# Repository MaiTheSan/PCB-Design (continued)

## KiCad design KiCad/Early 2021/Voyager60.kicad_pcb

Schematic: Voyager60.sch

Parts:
C1, C3, C4, C5, C9, C10, C11, C12, C13, C14, C15, C16, C17, C18, C19, C20, C21: 0.1uF; C_0603
C2: 10uF; C_0603
C6: 1uF; C_0603
C7, C8: 22pF; C_0603
D1, D2, D3, D4, D5, D6, D7, D8, D9, D10, D11, D12, D13, D14, D15, D16, D17, D18, D19, D20, D21, D22, D23, D24, D25, D26, D27, D28, D29, D30, D31, D32, D33, D34, D35, D36, D37, D38, D39, D40, D41, D42, D43, D45, D46, D47, D48, D49, D50, D51, D52, D53, D54, D55, D56, D57, D58, D59, D60, D61, D62, D63, D64, D65, D66, D67, D69: SOD-123; D_SOD-123
F1: 500mA; Fuse_SMD1206_Reflow
K_#1, K_#2, K_#3, K_#4, K_#5, K_#6, K_#7, K_#8, K_#9, K_#10: MX-1U; MXOnly-1U
K_'1: MX-1U; MXOnly-1U
K_,1: MX-1U; MXOnly-1U
K_-1: MX-1U; MXOnly-1U
K_.1: MX-1U; MXOnly-1U
K_/1: MX-1U; MXOnly-1U
K_;1: MX-1U; MXOnly-1U
K_=1: MX-1U; MXOnly-1U
K_A1: MX-1U; MXOnly-1U
K_ALT1: MX-1.25U; MXOnly-1.25U
K_ALT2: MX-1.5U; MXOnly-1.5U-FLIPPED
K_B1: MX-1U; MXOnly-1U
K_BACK1: MX-2U; MXOnly-2U
K_C1: MX-1U; MXOnly-1U
K_CAPS1: MX-1.75U; MXOnly-1.75U
K_CAPS2: MX-1.25U; MXOnly-1.25U-FLIPPED
K_CTRL1: MX-1.25U; MXOnly-1.25U
K_CTRL2: MX-1.5U; MXOnly-1.5U-FLIPPED
K_D1: MX-1U; MXOnly-1U
K_E1: MX-1U; MXOnly-1U
K_ENTER1: MX-2.25U; MXOnly-2.25U
K_ENTER2: MX-ISO; MXOnly-ISO-ROTATED-ReversedStabilizers
K_ESC1: MX-1U; MXOnly-1U
K_F1: MX-1U; MXOnly-1U
K_FNC1, K_FNC2, K_FNC3, K_FNC4, K_FNC5: MX-1U; MXOnly-1U-FLIPPED
K_G1: MX-1U; MXOnly-1U
K_H1: MX-1U; MXOnly-1U
K_I1: MX-1U; MXOnly-1U
K_J1: MX-1U; MXOnly-1U
K_K1: MX-1U; MXOnly-1U
K_L1: MX-1U; MXOnly-1U
K_M1: MX-1U; MXOnly-1U
K_N1: MX-1U; MXOnly-1U
K_O1: MX-1U; MXOnly-1U
K_P1: MX-1U; MXOnly-1U
K_Q1: MX-1U; MXOnly-1U
K_R1: MX-1U; MXOnly-1U
K_RALT2: MX-1.25U; MXOnly-1.25U-FLIPPED
K_RALT3: MX-1.5U; MXOnly-1.5U-FLIPPED
K_RCTRL2: MX-1U; MXOnly-1U
K_RMENU2: MX-1U; MXOnly-1U
K_RWIN2: MX-1.25U; MXOnly-1.25U
K_S1: MX-1U; MXOnly-1U
K_SHIFT1: MX-2.25U; MXOnly-2.25U
K_SPACE1: MX-7U; MXOnly-7U-ReversedStabilizers
K_SPACE2: MX-6.25U; MXOnly-6.25U-ReversedStabilizers
K_SRSHIFT1: MX-1.75U; MXOnly-1.75U
K_SRSHIFT2: MX-1U; MXOnly-1U
K_T1: MX-1U; MXOnly-1U
K_TAB1: MX-1.5U; MXOnly-1.5U
K_U1: MX-1U; MXOnly-1U
K_V1: MX-1U; MXOnly-1U
K_W1: MX-1U; MXOnly-1U
K_WIN1: MX-1.25U; MXOnly-1.25U
K_WIN2: MX-1U; MXOnly-1U-FLIPPED
K_X1: MX-1U; MXOnly-1U
K_Y1: MX-1U; MXOnly-1U
K_Z1: MX-1U; MXOnly-1U
K_[1: MX-1U; MXOnly-1U
K_\1: MX-1.5U; MXOnly-1.5U
K_\2: MX-1U; MXOnly-1U
K_]1: MX-1U; MXOnly-1U
Q1: 2N7002; SOT-23
R1, R2, R3, R4, R5, R6, R7, R8, R9, R10, R11, R12, R13, R14, R15, R16, R17, R18, R19, R20, R21, R22, R23, R24, R25, R26, R27, R28, R29, R30, R32, R33, R34, R35, R36, R37, R38, R39, R40, R41, R42, R43, R45, R46, R47, R48, R49, R50, R51, R52, R53, R54, R55, R56, R57, R58, R59, R60, R61, R62, R63, R64, R65, R66, R69, R71, R72, R76: 1k; R_0805
R31: 300; R_0805
R67, R68: 22; R_0805
R70: 10k; R_0805
R73, R74: 5.1k; R_0805
RGB1, RGB2, RGB3, RGB4, RGB5, RGB6, RGB7, RGB8, RGB9, RGB10, RGB11, RGB12, RGB13, RGB14: WS2812B
SW1: 5.2x5.2mm; SKQG-1155865
U1: ATmega32U4-MU; QFN-44-1EP_7x7mm_Pitch0.5mm
U2: PRTR5V0U2X; SOT143B
U3: STF202-22T1G; Reset_Pretty
USB1: HRO-TYPE-C-31-M-12; HRO-TYPE-C-31-M-12-Assembly
Y1: 16Mhz; Crystal_SMD_3225-4Pin_3.2x2.5mm

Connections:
+5V: C1.2, C2.2, C3.2, C4.2, C5.2, C9.2, C10.2, C11.2, C12.2, C13.2, C14.2, C15.2, C16.2, C17.2, C18.2, C19.2, C20.2, C21.2, F1.1, K_#1.3, K_#2.3, K_#3.3, K_#4.3, K_#5.3, K_#6.3, K_#7.3, K_#8.3, K_#9.3, K_#10.3, K_'1.3, K_,1.3, K_-1.3, K_.1.3, K_/1.3, K_;1.3, K_=1.3, K_A1.3, K_ALT1.3, K_ALT2.3, K_B1.3, K_BACK1.3, K_C1.3, K_CAPS1.3, K_CAPS2.3, K_CTRL1.3, K_CTRL2.3, K_D1.3, K_E1.3, K_ENTER1.3, K_ENTER2.3, K_ESC1.3, K_F1.3, K_FNC1.3, K_FNC2.3, K_FNC3.3, K_FNC4.3, K_FNC5.3, K_G1.3, K_H1.3, K_I1.3, K_J1.3, K_K1.3, K_L1.3, K_M1.3, K_N1.3, K_O1.3, K_P1.3, K_Q1.3, K_R1.3, K_RALT2.3, K_RALT3.3, K_RCTRL2.3, K_RMENU2.3, K_RWIN2.3, K_S1.3, K_SHIFT1.3, K_SPACE1.3, K_SPACE2.3, K_SRSHIFT1.3, K_SRSHIFT2.3, K_T1.3, K_TAB1.3, K_U1.3, K_V1.3, K_W1.3, K_WIN1.3, K_WIN2.3, K_X1.3, K_Y1.3, K_Z1.3, K_[1.3, K_\1.3, K_\2.3, K_]1.3, R70.1, RGB1.1, RGB2.1, RGB3.1, RGB4.1, RGB5.1, RGB6.1, RGB7.1, RGB8.1, RGB9.1, RGB10.1, RGB11.1, RGB12.1, RGB13.1, RGB14.1, U1.2, U1.7, U1.14, U1.24, U1.34, U1.44, U3.2 (DIN1)
COL0: K_CAPS1.1, K_CAPS2.2, K_CTRL1.1, K_CTRL2.1, K_ESC1.1, K_SHIFT1.1, K_TAB1.1, U1.39
COL1: K_#1.1, K_A1.1, K_Q1.1, K_WIN1.1, K_WIN2.1, U1.36
COL2: K_#2.1, K_ALT1.1, K_ALT2.1, K_S1.1, K_W1.1, K_Z1.1, U1.38
COL3: K_#3.1, K_D1.1, K_E1.1, K_X1.1, U1.37
COL4: K_#4.1, K_C1.1, K_F1.1, K_R1.1, U1.32
COL5: K_#5.1, K_G1.1, K_T1.1, K_V1.1, U1.31
COL6: K_#6.1, K_B1.1, K_H1.1, K_SPACE1.1, K_SPACE2.1, K_Y1.1, U1.30
COL7: K_#7.1, K_J1.1, K_N1.1, K_U1.1, U1.29
COL8: K_#8.1, K_I1.1, K_K1.1, K_M1.1, U1.28
COL9: K_#9.1, K_,1.1, K_L1.1, K_O1.1, U1.27
COL10: K_#10.1, K_.1.1, K_;1.1, K_P1.1, K_RALT2.1, U1.26
COL11: K_'1.1, K_-1.1, K_/1.1, K_RALT3.1, K_RWIN2.1, K_[1.1, U1.25
COL12: K_=1.1, K_RMENU2.1, K_SRSHIFT1.1, K_]1.1, U1.22
COL13: K_BACK1.1, K_ENTER1.1, K_ENTER2.1, K_RCTRL2.1, K_SRSHIFT2.1, K_\1.1, K_\2.1, U1.21
COL14: K_FNC1.1, K_FNC2.1, K_FNC3.1, K_FNC4.1, K_FNC5.1, U1.20
CapLockLed: R31.2, U1.18
D+: R68.1, U1.4
D-: R67.1, U1.3
GND: C1.1, C2.1, C3.1, C4.1, C5.1, C6.2, C7.2, C8.2, C9.1, C10.1, C11.1, C12.1, C13.1, C14.1, C15.1, C16.1, C17.1, C18.1, C19.1, C20.1, C21.1, Q1.2, R71.1, R73.1, R74.1, RGB1.3, RGB2.3, RGB3.3, RGB4.3, RGB5.3, RGB6.3, RGB7.3, RGB8.3, RGB9.3, RGB10.3, RGB11.3, RGB12.3, RGB13.3, RGB14.3, SW1.1, U1.5, U1.15, U1.23, U1.35, U1.43, U1.45, U2.1, U3.6 (GND), USB1.1, USB1.12, USB1.13, Y1.2, Y1.4
LEDGND: Q1.3, R1.2, R2.2, R3.2, R4.2, R5.2, R6.2, R7.2, R8.2, R9.2, R10.2, R11.2, R12.2, R13.2, R14.2, R15.2, R16.2, R17.2, R18.2, R19.2, R20.2, R21.2, R22.2, R23.2, R24.2, R25.2, R26.2, R27.2, R28.2, R29.2, R30.2, R32.2, R33.2, R34.2, R35.2, R36.2, R37.2, R38.2, R39.2, R40.2, R41.2, R42.2, R43.2, R45.2, R46.2, R47.2, R48.2, R49.2, R50.2, R51.2, R52.2, R53.2, R54.2, R55.2, R56.2, R57.2, R58.2, R59.2, R60.2, R61.2, R62.2, R63.2, R64.2, R65.2, R66.2, R72.2, R76.2
unnamed: C6.1, U1.6
unnamed: C7.1, U1.17, Y1.1
unnamed: C8.1, U1.16, Y1.3
unnamed: D1.2, K_ESC1.2
unnamed: D2.2, K_#1.2
unnamed: D3.2, K_#2.2
unnamed: D4.2, K_#3.2
unnamed: D5.2, K_#4.2
unnamed: D6.2, K_#5.2
unnamed: D7.2, K_#6.2
unnamed: D8.2, K_#7.2
unnamed: D9.2, K_#8.2
unnamed: D10.2, K_#9.2
unnamed: D11.2, K_#10.2
unnamed: D12.2, K_-1.2
unnamed: D13.2, K_=1.2
unnamed: D14.2, K_BACK1.2
unnamed: D15.2, K_FNC1.2
unnamed: D16.2, K_TAB1.2
unnamed: D17.2, K_Q1.2
unnamed: D18.2, K_W1.2
unnamed: D19.2, K_E1.2
unnamed: D20.2, K_R1.2
unnamed: D21.2, K_T1.2
unnamed: D22.2, K_Y1.2
unnamed: D23.2, K_U1.2
unnamed: D24.2, K_I1.2
unnamed: D25.2, K_O1.2
unnamed: D26.2, K_P1.2
unnamed: D27.2, K_[1.2
unnamed: D28.2, K_]1.2
unnamed: D29.2, K_\1.2, K_\2.2
unnamed: D30.2, K_RMENU2.2
unnamed: D31.2, K_CAPS1.2, K_CAPS2.1
unnamed: D32.2, K_A1.2
unnamed: D33.2, K_S1.2
unnamed: D34.2, K_D1.2
unnamed: D35.2, K_F1.2
unnamed: D36.2, K_G1.2
unnamed: D37.2, K_H1.2
unnamed: D38.2, K_J1.2
unnamed: D39.2, K_K1.2
unnamed: D40.2, K_L1.2
unnamed: D41.2, K_;1.2
unnamed: D42.2, K_'1.2
unnamed: D43.2, K_ENTER1.2, K_ENTER2.2
unnamed: D45.2, K_SHIFT1.2
unnamed: D46.2, K_Z1.2
unnamed: D47.2, K_X1.2
unnamed: D48.2, K_C1.2
unnamed: D49.2, K_V1.2
unnamed: D50.2, K_B1.2
unnamed: D51.2, K_N1.2
unnamed: D52.2, K_M1.2
unnamed: D53.2, K_,1.2
unnamed: D54.2, K_.1.2
unnamed: D55.2, K_/1.2
unnamed: D56.2, K_SRSHIFT1.2
unnamed: D57.2, K_SRSHIFT2.2
unnamed: D58.2, K_FNC2.2
unnamed: D59.2, K_CTRL1.2, K_CTRL2.2
unnamed: D60.2, K_WIN1.2, K_WIN2.2
unnamed: D61.2, K_SPACE1.2, K_SPACE2.2
unnamed: D62.2, K_FNC3.2
unnamed: D63.2, K_RALT2.2
unnamed: D64.2, K_RALT3.2, K_RWIN2.2
unnamed: D65.2, K_RCTRL2.2
unnamed: D66.2, K_FNC4.2
unnamed: D67.2, K_ALT1.2, K_ALT2.2
unnamed: D69.2, K_FNC5.2
unnamed: K_#1.4, R2.1
unnamed: K_#2.4, R3.1
unnamed: K_#3.4, R4.1
unnamed: K_#4.4, R5.1
unnamed: K_#5.4, R6.1
unnamed: K_#6.4, R7.1
unnamed: K_#7.4, R8.1
unnamed: K_#8.4, R9.1
unnamed: K_#9.4, R10.1
unnamed: K_#10.4, R11.1
unnamed: K_'1.4, R42.1
unnamed: K_,1.4, R53.1
unnamed: K_-1.4, R12.1
unnamed: K_.1.4, R54.1
unnamed: K_/1.4, R55.1
unnamed: K_;1.4, R41.1
unnamed: K_=1.4, R13.1
unnamed: K_A1.4, R32.1
unnamed: K_ALT1.4, K_ALT2.4, R72.1
unnamed: K_B1.4, R50.1
unnamed: K_BACK1.4, R14.1
unnamed: K_C1.4, R48.1
unnamed: K_CAPS1.4, K_CAPS2.4, R31.1
unnamed: K_CTRL1.4, K_CTRL2.4, R59.1
unnamed: K_D1.4, R34.1
unnamed: K_E1.4, R19.1
unnamed: K_ENTER1.4, K_ENTER2.4, R43.1
unnamed: K_ESC1.4, R1.1
unnamed: K_F1.4, R35.1
unnamed: K_FNC1.4, R15.1
unnamed: K_FNC2.4, R58.1
unnamed: K_FNC3.4, R62.1
unnamed: K_FNC4.4, R66.1
unnamed: K_FNC5.4, R76.1
unnamed: K_G1.4, R36.1
unnamed: K_H1.4, R37.1
unnamed: K_I1.4, R24.1
unnamed: K_J1.4, R38.1
unnamed: K_K1.4, R39.1
unnamed: K_L1.4, R40.1
unnamed: K_M1.4, R52.1
unnamed: K_N1.4, R51.1
unnamed: K_O1.4, R25.1
unnamed: K_P1.4, R26.1
unnamed: K_Q1.4, R17.1
unnamed: K_R1.4, R20.1
unnamed: K_RALT2.4, R63.1
unnamed: K_RALT3.4, K_RWIN2.4, R64.1
unnamed: K_RCTRL2.4, R65.1
unnamed: K_RMENU2.4, R30.1
unnamed: K_S1.4, R33.1
unnamed: K_SHIFT1.4, R45.1
unnamed: K_SPACE1.4, K_SPACE2.4, R61.1
unnamed: K_SRSHIFT1.4, R56.1
unnamed: K_SRSHIFT2.4, R57.1
unnamed: K_T1.4, R21.1
unnamed: K_TAB1.4, R16.1
unnamed: K_U1.4, R23.1
unnamed: K_V1.4, R49.1
unnamed: K_W1.4, R18.1
unnamed: K_WIN1.4, K_WIN2.4, R60.1
unnamed: K_X1.4, R47.1
unnamed: K_Y1.4, R22.1
unnamed: K_Z1.4, R46.1
unnamed: K_[1.4, R27.1
unnamed: K_\1.4, K_\2.4, R29.1
unnamed: K_]1.4, R28.1
unnamed: Q1.1, R69.1
unnamed: R67.2, U2.3, USB1.5, USB1.7
unnamed: R68.2, U2.2, USB1.6, USB1.8
unnamed: R69.2, U1.12
unnamed: R70.2, SW1.2, U1.13, U3.5 (DOUT1)
unnamed: R71.2, U1.33
unnamed: R73.2, USB1.4
unnamed: R74.2, USB1.10
unnamed: RGB1.2, RGB3.4
unnamed: RGB2.2, RGB4.4
unnamed: RGB3.2, RGB5.4
unnamed: RGB4.2, RGB6.4
unnamed: RGB5.2, RGB7.4
unnamed: RGB6.2, RGB8.4
unnamed: RGB7.2, RGB9.4
unnamed: RGB10.2, RGB12.4
unnamed: RGB8.2, RGB10.4
unnamed: RGB11.2, RGB13.4
unnamed: RGB9.2, RGB11.4
unnamed: RGB12.2, RGB14.4
unnamed: RGB2.4, RGB13.2
RGBLED: RGB1.4, U1.19
ROW0: D1.1, D2.1, D3.1, D4.1, D5.1, D6.1, D7.1, D8.1, D9.1, D10.1, D11.1, D12.1, D13.1, D14.1, D15.1, U1.9, U3.3 (DIN2)
ROW1: D16.1, D17.1, D18.1, D19.1, D20.1, D21.1, D22.1, D23.1, D24.1, D25.1, D26.1, D27.1, D28.1, D29.1, D58.1, U1.10, U3.4 (DOUT2)
ROW2: D31.1, D32.1, D33.1, D34.1, D35.1, D36.1, D37.1, D38.1, D39.1, D40.1, D41.1, D42.1, D43.1, D62.1, U1.11, U3.1 (VBUS)
ROW3: D45.1, D46.1, D47.1, D48.1, D49.1, D50.1, D51.1, D52.1, D53.1, D54.1, D55.1, D56.1, D57.1, D66.1, U1.41
ROW4: D30.1, D59.1, D60.1, D61.1, D63.1, D64.1, D65.1, D67.1, D69.1, U1.40
VCC: F1.2, U2.4, USB1.2, USB1.11

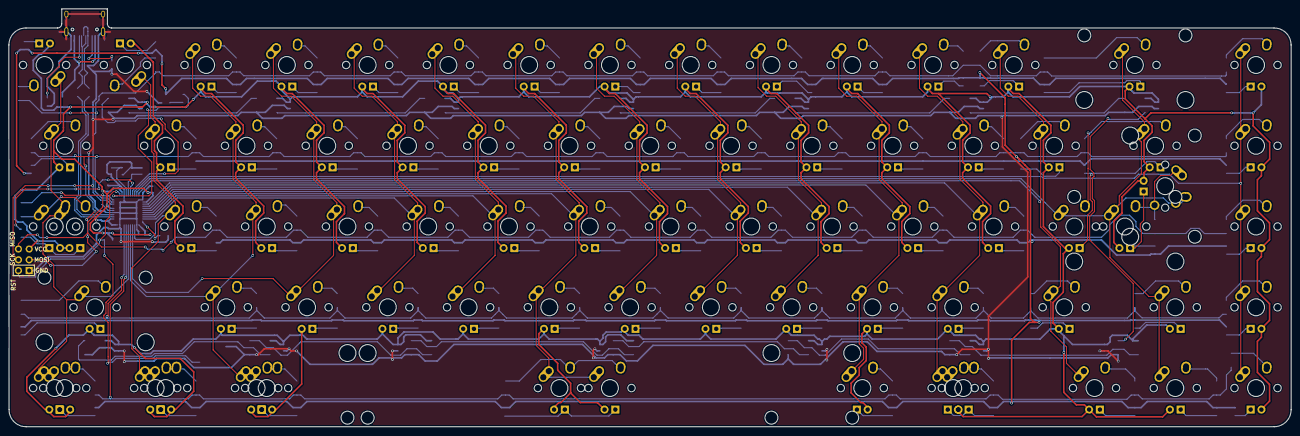
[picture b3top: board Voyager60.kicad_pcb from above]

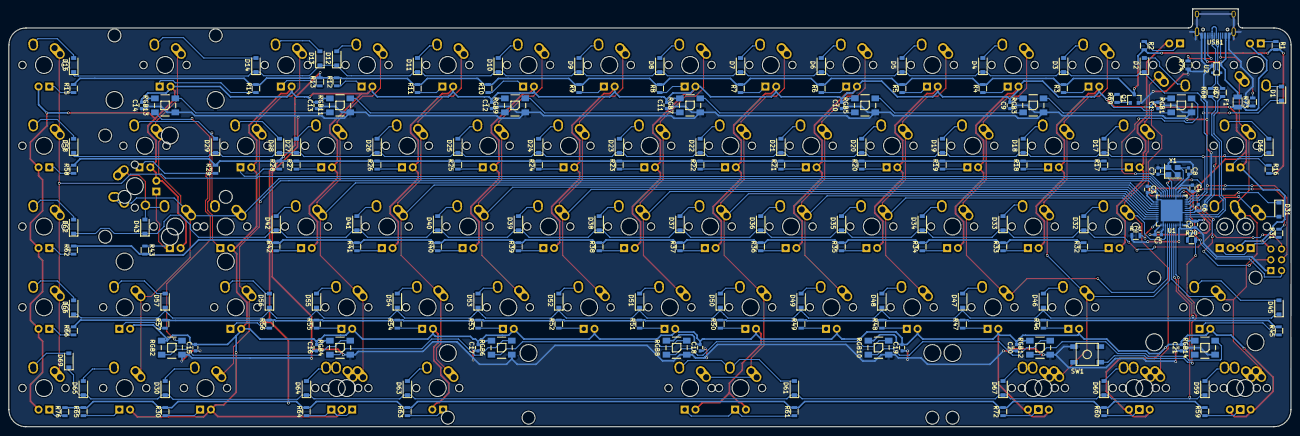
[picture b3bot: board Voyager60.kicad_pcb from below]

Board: 2 copper layers, 302.4 x 98.5 mm, 259 parts (183 on the bottom side), 186 nets.

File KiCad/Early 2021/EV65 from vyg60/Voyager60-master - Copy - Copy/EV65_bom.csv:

Component,Description,Part,References,Value,Footprint,Quantity Per PCB,Datasheet
1,"Capacitor, Ceramic, 15V or more",C_Small,C1 C3 C4 C5 C9 C10 C11 C12 C13 C14 C15 C16 C17 C18 C19 C20 C21,0.1uF,C_0603,17,
2,"Capacitor, Ceramic, 15V or more",C_Small,C2,10uF,C_0603,1,
3,"Capacitor, Ceramic, 15V or more",C_Small,C6,1uF,C_0603,1,
4,"Capacitor, Ceramic, 15V or more",C_Small,C7 C8,22pF,C_0603,2,
5,"Diode, Generic",D_Small,D1 D2 D3 D4 D5 D6 D7 D8 D9 D10 D11 D12 D13 D14 D16 D17 D18 D19 D20 D21 D22 D23 D24 D25 D26 D27 D28 D29 D30 D31 D32 D33 D34 D35 D36 D37 D38 D39 D40 D41 D42 D43 D45 D46 D47 D48 D49 D50 D51 D52 D53 D54 D55 D56 D57 D58 D59 D60 D61 D62 D63 D64 D65 D67 D69,SOD-123,D_SOD-123,66,
6,"Polyfuse, 500mA hold, 1A trip",Polyfuse_Small,F1,500mA,Fuse_SMD1206_Reflow,1,
7,N-Channel MOSFET,2N7002,Q1,2N7002,SOT-23,1,https://www.fairchildsemi.com/datasheets/2N/2N7002.pdf
8,"Resistor, Generic",R_Small,R70,10k,R_0805,1,
9,"resistor, Generic",R_Small,R31,300,R_0805,1,
10,"Resistor, Generic",R_Small,R1 R2 R3 R4 R5 R6 R7 R8 R9 R10 R11 R12 R13 R14 R16 R17 R18 R19 R20 R21 R22 R23 R24 R25 R26 R27 R28 R29 R30 R32 R33 R34 R35 R36 R37 R38 R39 R40 R41 R42 R43 R45 R46 R47 R48 R49 R50 R51 R52 R53 R54 R55 R56 R57 R58 R59 R60 R61 R62 R63 R64 R65 R66 R69 R71 R72 R76,1k,R_0805,69,
11,"Resistor, Generic",R_Small,R67 R68,22,R_0805,2,
12,"Resistor, Generic",R_Small,R73 R74,5.1k,R_0805,2,
13,"WS2812B RGB LED, 5050",WS2812B,RGB1 RGB2 RGB3 RGB4 RGB5 RGB6 RGB7 RGB8 RGB9 RGB10 RGB11 RGB12 RGB13 RGB14,WS2812B,WS2812B,14,
14,"5.2 x 5.2mm Push Button, SMT",SW_Push,SW1,5.2x5.2mm,SKQG-1155865,1,
15,ATmega32U4-MU,ATmega32U4-MU-MCU_Microchip_ATmega,U1,ATmega32U4-MU,QFN-44-1EP_7x7mm_Pitch0.5mm,1,http://ww1.microchip.com/downloads/en/DeviceDoc/Atmel-7766-8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
16,ESD Protection IC,PRTR5V0U2X,U2,PRTR5V0U2X,SOT143B,1,
17,USB Type-C Connector,HRO-TYPE-C-31-M-12,USB1,HRO-TYPE-C-31-M-12,HRO-TYPE-C-31-M-12-Assembly,1,
18,"Crystal, 3.2 x 2.5mm, 16MHz",Crystal_GND24,Y1,16Mhz,Crystal_SMD_3225-4pin_3.2x2.5mm,1,

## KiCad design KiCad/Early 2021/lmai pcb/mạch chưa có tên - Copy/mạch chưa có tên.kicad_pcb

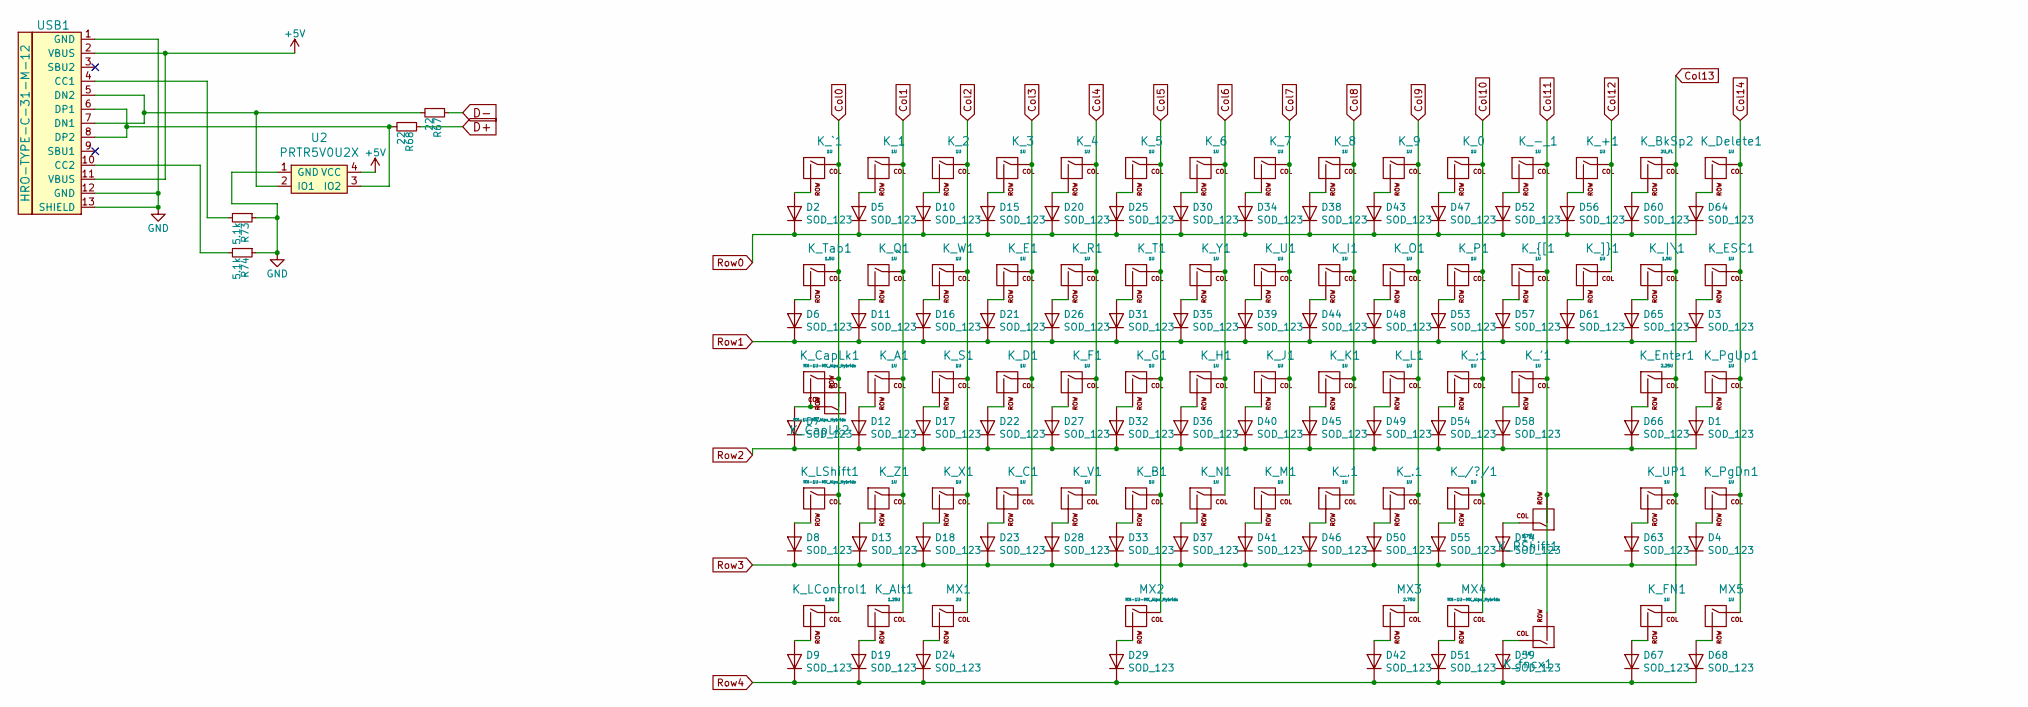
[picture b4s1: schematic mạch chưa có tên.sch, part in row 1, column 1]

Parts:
D1, D2, D3, D4, D5, D6, D7, D8, D9, D10, D11, D12, D13, D14, D15, D16, D17, D18, D19, D20, D21, D22, D23, D24, D25, D26, D27, D28, D29, D30, D31, D32, D33, D34, D35, D36, D37, D38, D39, D40, D41, D42, D43, D44, D45, D46, D47, D48, D49, D50, D51, D52, D53, D54, D55, D56, D57, D58, D59, D60, D61, D63, D64, D65, D66, D67, D68: SOD_123; D_SOD-123
K_0, K_1, K_2, K_3, K_4, K_5, K_6, K_7, K_8, K_9, K_.1: 1U; MXOnly-1U-NoLED
K_'1: 1U; MXOnly-1U-NoLED
K_+1: 1U; MXOnly-1U-NoLED
K_,1: 1U; MXOnly-1U-NoLED
K_-_1: 1U; MXOnly-1U-NoLED
K_/?/1: 1U; MXOnly-1U-NoLED
K_;1: 1U; MXOnly-1U-NoLED
K_A1: 1U; MXOnly-1U-NoLED
K_Alt1: 1.25U; MXOnly-1.25U-NoLED
K_B1: 1U; MXOnly-1U-NoLED
K_BkSp2: 2U_FL; MXOnly-2U-ReversedStabilizers-NoLED
K_C1: 1U; MXOnly-1U-NoLED
K_CapLk1: MX-1U-MX_Alps_Hybrids; MXOnly-1.75U-NoLED
K_CapLk2: MX-1U-MX_Alps_Hybrids; MXOnly-1.25U-NoLED
K_D1: 1U; MXOnly-1U-NoLED
K_Delete1: 1U; MXOnly-1U-NoLED
K_E1: 1U; MXOnly-1U-NoLED
K_ESC1: 1U; MXOnly-1U-NoLED
K_Enter1: 2.25U; MXOnly-2.25U-ReversedStabilizers-NoLED
K_F1: 1U; MXOnly-1U-NoLED
K_FN1: 1U; MXOnly-1U-NoLED
K_G1: 1U; MXOnly-1U-NoLED
K_H1: 1U; MXOnly-1U-NoLED
K_I1: 1U; MXOnly-1U-NoLED
K_J1: 1U; MXOnly-1U-NoLED
K_K1: 1U; MXOnly-1U-NoLED
K_L1: 1U; MXOnly-1U-NoLED
K_LControl1: 1.5U; MXOnly-1.25U-NoLED
K_LShift1: MX-1U-MX_Alps_Hybrids; MXOnly-2.25U-ReversedStabilizers-NoLED
K_M1: 1U; MXOnly-1U-NoLED
K_N1: 1U; MXOnly-1U-NoLED
K_O1: 1U; MXOnly-1U-NoLED
K_P1: 1U; MXOnly-1U-NoLED
K_PgDn1: 1U; MXOnly-1U-NoLED
K_PgUp1: 1U; MXOnly-1U-NoLED
K_Q1: 1U; MXOnly-1U-NoLED
K_R1: 1U; MXOnly-1U-NoLED
K_RShift1: 1.75U; MXOnly-1.75U-NoLED
K_S1: 1U; MXOnly-1U-NoLED
K_T1: 1U; MXOnly-1U-NoLED
K_Tab1: 1.5U; MXOnly-1.5U-NoLED
K_U1: 1U; MXOnly-1U-NoLED
K_UP1: 1U; MXOnly-1U-NoLED
K_V1: 1U; MXOnly-1U-NoLED
K_W1: 1U; MXOnly-1U-NoLED
K_X1: 1U; MXOnly-1U-NoLED
K_Y1: 1U; MXOnly-1U-NoLED
K_Z1: 1U; MXOnly-1U-NoLED
K_]}1: 1U; MXOnly-1U-NoLED
K_`1: 1U; MXOnly-1U-NoLED
K_fncx1: 1U; MXOnly-1U-NoLED
K_{[1: 1U; MXOnly-1U-NoLED
K_|\1: 1.5U; MXOnly-1.5U-NoLED
MX1: 2U; MXOnly-1.25U-NoLED
MX2: MX-1U-MX_Alps_Hybrids; MXOnly-6.25U-NoLED
MX3: 2.75U; MXOnly-1.25U-NoLED
MX4: MX-1U-MX_Alps_Hybrids; MXOnly-1.25U-NoLED
MX5: 1U; MXOnly-1U-NoLED
R67, R68: 22; C_0603
R73, R74: 5.1k; C_0603
U2: PRTR5V0U2X; SOT143B
USB1: HRO-TYPE-C-31-M-12; HRO-TYPE-C-31-M-12-Assembly

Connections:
+5V: U2.4 (VCC), USB1.2 (VBUS), USB1.11 (VBUS)
Col0: K_CapLk1.1 (COL), K_CapLk2.2 (ROW), K_LControl1.1 (COL), K_LShift1.1 (COL), K_Tab1.1 (COL), K_`1.1 (COL)
Col1: K_1.1 (COL), K_A1.1 (COL), K_Alt1.1 (COL), K_Q1.1 (COL), K_Z1.1 (COL)
Col2: K_2.1 (COL), K_S1.1 (COL), K_W1.1 (COL), K_X1.1 (COL), MX1.1 (COL)
Col3: K_3.1 (COL), K_C1.1 (COL), K_D1.1 (COL), K_E1.1 (COL)
Col4: K_4.1 (COL), K_F1.1 (COL), K_R1.1 (COL), K_V1.1 (COL)
Col5: K_5.1 (COL), K_B1.1 (COL), K_G1.1 (COL), K_T1.1 (COL), MX2.1 (COL)
Col6: K_6.1 (COL), K_H1.1 (COL), K_N1.1 (COL), K_Y1.1 (COL)
Col7: K_7.1 (COL), K_J1.1 (COL), K_M1.1 (COL), K_U1.1 (COL)
Col8: K_8.1 (COL), K_,1.1 (COL), K_I1.1 (COL), K_K1.1 (COL)
Col9: K_9.1 (COL), K_.1.1 (COL), K_L1.1 (COL), K_O1.1 (COL), MX3.1 (COL)
Col10: K_0.1 (COL), K_/?/1.1 (COL), K_;1.1 (COL), K_P1.1 (COL), MX4.1 (COL)
Col11: K_'1.1 (COL), K_-_1.1 (COL), K_RShift1.2 (ROW), K_fncx1.2 (ROW), K_{[1.1 (COL)
Col12: K_+1.1 (COL), K_]}1.1 (COL)
Col13: K_BkSp2.1 (COL), K_Enter1.1 (COL), K_FN1.1 (COL), K_UP1.1 (COL), K_|\1.1 (COL)
Col14: K_Delete1.1 (COL), K_ESC1.1 (COL), K_PgDn1.1 (COL), K_PgUp1.1 (COL), MX5.1 (COL)
GND: R73.1, R74.1, U2.1 (GND), USB1.1 (GND), USB1.12 (GND), USB1.13 (SHIELD)
unnamed: D1.2 (A), K_PgUp1.2 (ROW)
unnamed: D2.2 (A), K_`1.2 (ROW)
unnamed: D3.2 (A), K_ESC1.2 (ROW)
unnamed: D4.2 (A), K_PgDn1.2 (ROW)
unnamed: D5.2 (A), K_1.2 (ROW)
unnamed: D6.2 (A), K_Tab1.2 (ROW)
unnamed: D7.2 (A), K_CapLk1.2 (ROW), K_CapLk2.1 (COL)
unnamed: D8.2 (A), K_LShift1.2 (ROW)
unnamed: D9.2 (A), K_LControl1.2 (ROW)
unnamed: D10.2 (A), K_2.2 (ROW)
unnamed: D11.2 (A), K_Q1.2 (ROW)
unnamed: D12.2 (A), K_A1.2 (ROW)
unnamed: D13.2 (A), K_Z1.2 (ROW)
unnamed: D14.2 (A), K_RShift1.1 (COL)
unnamed: D15.2 (A), K_3.2 (ROW)
unnamed: D16.2 (A), K_W1.2 (ROW)
unnamed: D17.2 (A), K_S1.2 (ROW)
unnamed: D18.2 (A), K_X1.2 (ROW)
unnamed: D19.2 (A), K_Alt1.2 (ROW)
unnamed: D20.2 (A), K_4.2 (ROW)
unnamed: D21.2 (A), K_E1.2 (ROW)
unnamed: D22.2 (A), K_D1.2 (ROW)
unnamed: D23.2 (A), K_C1.2 (ROW)
unnamed: D24.2 (A), MX1.2 (ROW)
unnamed: D25.2 (A), K_5.2 (ROW)
unnamed: D26.2 (A), K_R1.2 (ROW)
unnamed: D27.2 (A), K_F1.2 (ROW)
unnamed: D28.2 (A), K_V1.2 (ROW)
unnamed: D29.2 (A), MX2.2 (ROW)
unnamed: D30.2 (A), K_6.2 (ROW)
unnamed: D31.2 (A), K_T1.2 (ROW)
unnamed: D32.2 (A), K_G1.2 (ROW)
unnamed: D33.2 (A), K_B1.2 (ROW)
unnamed: D34.2 (A), K_7.2 (ROW)
unnamed: D35.2 (A), K_Y1.2 (ROW)
unnamed: D36.2 (A), K_H1.2 (ROW)
unnamed: D37.2 (A), K_N1.2 (ROW)
unnamed: D38.2 (A), K_8.2 (ROW)
unnamed: D39.2 (A), K_U1.2 (ROW)
unnamed: D40.2 (A), K_J1.2 (ROW)
unnamed: D41.2 (A), K_M1.2 (ROW)
unnamed: D42.2 (A), MX3.2 (ROW)
unnamed: D43.2 (A), K_9.2 (ROW)
unnamed: D44.2 (A), K_I1.2 (ROW)
unnamed: D45.2 (A), K_K1.2 (ROW)
unnamed: D46.2 (A), K_,1.2 (ROW)
unnamed: D47.2 (A), K_0.2 (ROW)
unnamed: D48.2 (A), K_O1.2 (ROW)
unnamed: D49.2 (A), K_L1.2 (ROW)
unnamed: D50.2 (A), K_.1.2 (ROW)
unnamed: D51.2 (A), MX4.2 (ROW)
unnamed: D52.2 (A), K_-_1.2 (ROW)
unnamed: D53.2 (A), K_P1.2 (ROW)
unnamed: D54.2 (A), K_;1.2 (ROW)
unnamed: D55.2 (A), K_/?/1.2 (ROW)
unnamed: D56.2 (A), K_+1.2 (ROW)
unnamed: D57.2 (A), K_{[1.2 (ROW)
unnamed: D58.2 (A), K_'1.2 (ROW)
unnamed: D59.2 (A), K_fncx1.1 (COL)
unnamed: D60.2 (A), K_BkSp2.2 (ROW)
unnamed: D61.2 (A), K_]}1.2 (ROW)
unnamed: D63.2 (A), K_UP1.2 (ROW)
unnamed: D64.2 (A), K_Delete1.2 (ROW)
unnamed: D65.2 (A), K_|\1.2 (ROW)
unnamed: D66.2 (A), K_Enter1.2 (ROW)
unnamed: D67.2 (A), K_FN1.2 (ROW)
unnamed: D68.2 (A), MX5.2 (ROW)
unnamed: R67.2, U2.2 (IO1), USB1.5 (DN2), USB1.7 (DN1)
unnamed: R68.2, U2.3 (IO2), USB1.6 (DP1), USB1.8 (DP2)
unnamed: R73.2, USB1.4 (CC1)
unnamed: R74.2, USB1.10 (CC2)
Row0: D2.1 (K), D5.1 (K), D10.1 (K), D15.1 (K), D20.1 (K), D25.1 (K), D30.1 (K), D34.1 (K), D38.1 (K), D43.1 (K), D47.1 (K), D52.1 (K), D56.1 (K), D60.1 (K), D64.1 (K)
Row1: D3.1 (K), D6.1 (K), D11.1 (K), D16.1 (K), D21.1 (K), D26.1 (K), D31.1 (K), D35.1 (K), D39.1 (K), D44.1 (K), D48.1 (K), D53.1 (K), D57.1 (K), D61.1 (K), D65.1 (K)
Row2: D1.1 (K), D7.1 (K), D12.1 (K), D17.1 (K), D22.1 (K), D27.1 (K), D32.1 (K), D36.1 (K), D40.1 (K), D45.1 (K), D49.1 (K), D54.1 (K), D58.1 (K), D66.1 (K)
Row3: D4.1 (K), D8.1 (K), D13.1 (K), D14.1 (K), D18.1 (K), D23.1 (K), D28.1 (K), D33.1 (K), D37.1 (K), D41.1 (K), D46.1 (K), D50.1 (K), D55.1 (K), D63.1 (K)
Row4: D9.1 (K), D19.1 (K), D24.1 (K), D29.1 (K), D42.1 (K), D51.1 (K), D59.1 (K), D67.1 (K), D68.1 (K)

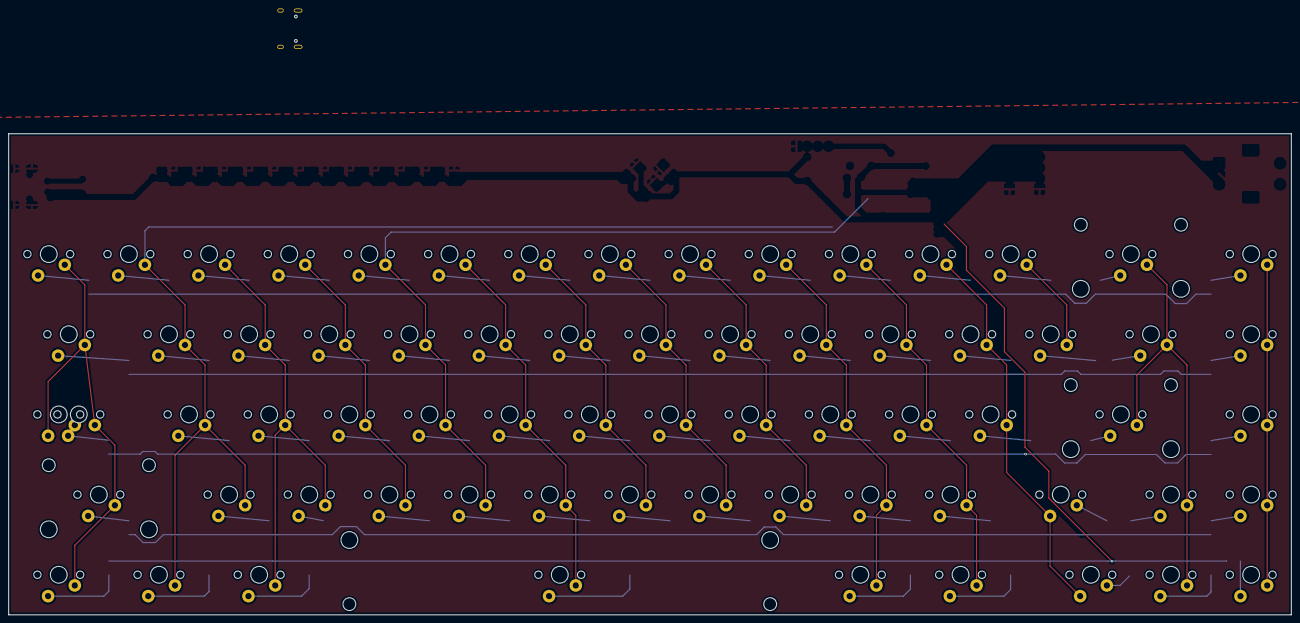
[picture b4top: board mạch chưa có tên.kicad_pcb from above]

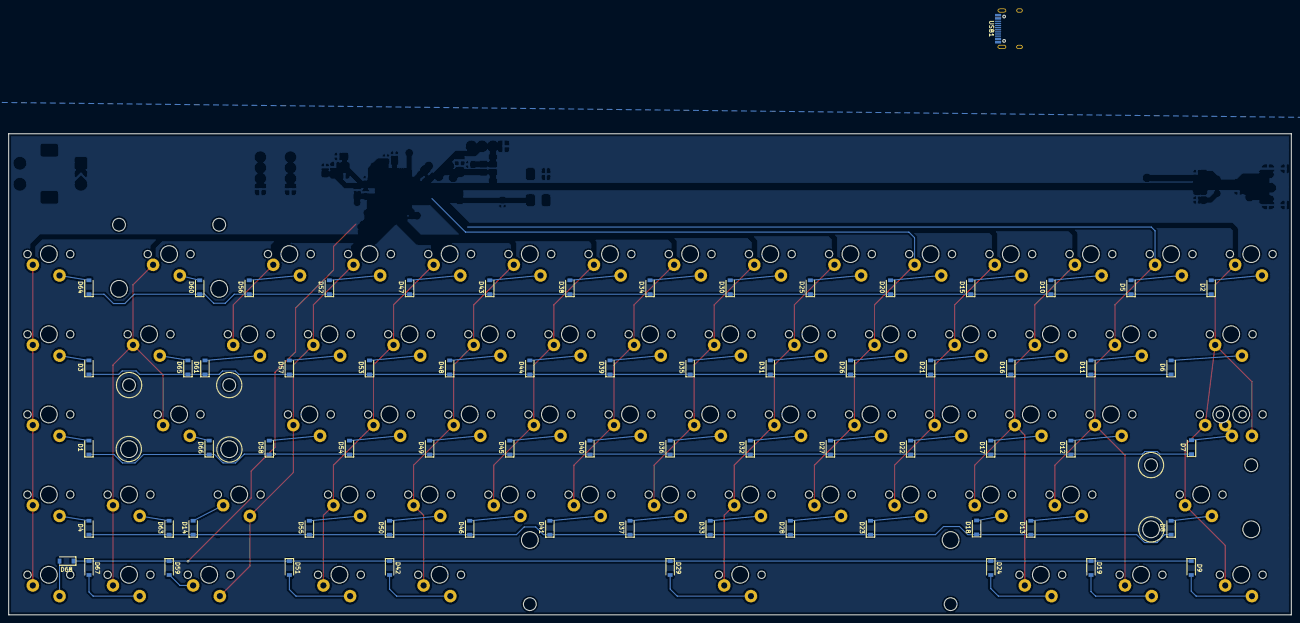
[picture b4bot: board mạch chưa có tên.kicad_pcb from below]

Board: 2 copper layers, 304.8 x 114.3 mm, 136 parts (68 on the bottom side), 91 nets.
